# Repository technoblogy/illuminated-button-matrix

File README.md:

# Illuminated Button Matrix
A 4 x 4 matrix of illuminated pushbuttons with a two-wire I2C interface, controlled by an ATtiny88, that you can use for games, music, or control applications.
For more information see: http://www.technoblogy.com/show?1YJO.

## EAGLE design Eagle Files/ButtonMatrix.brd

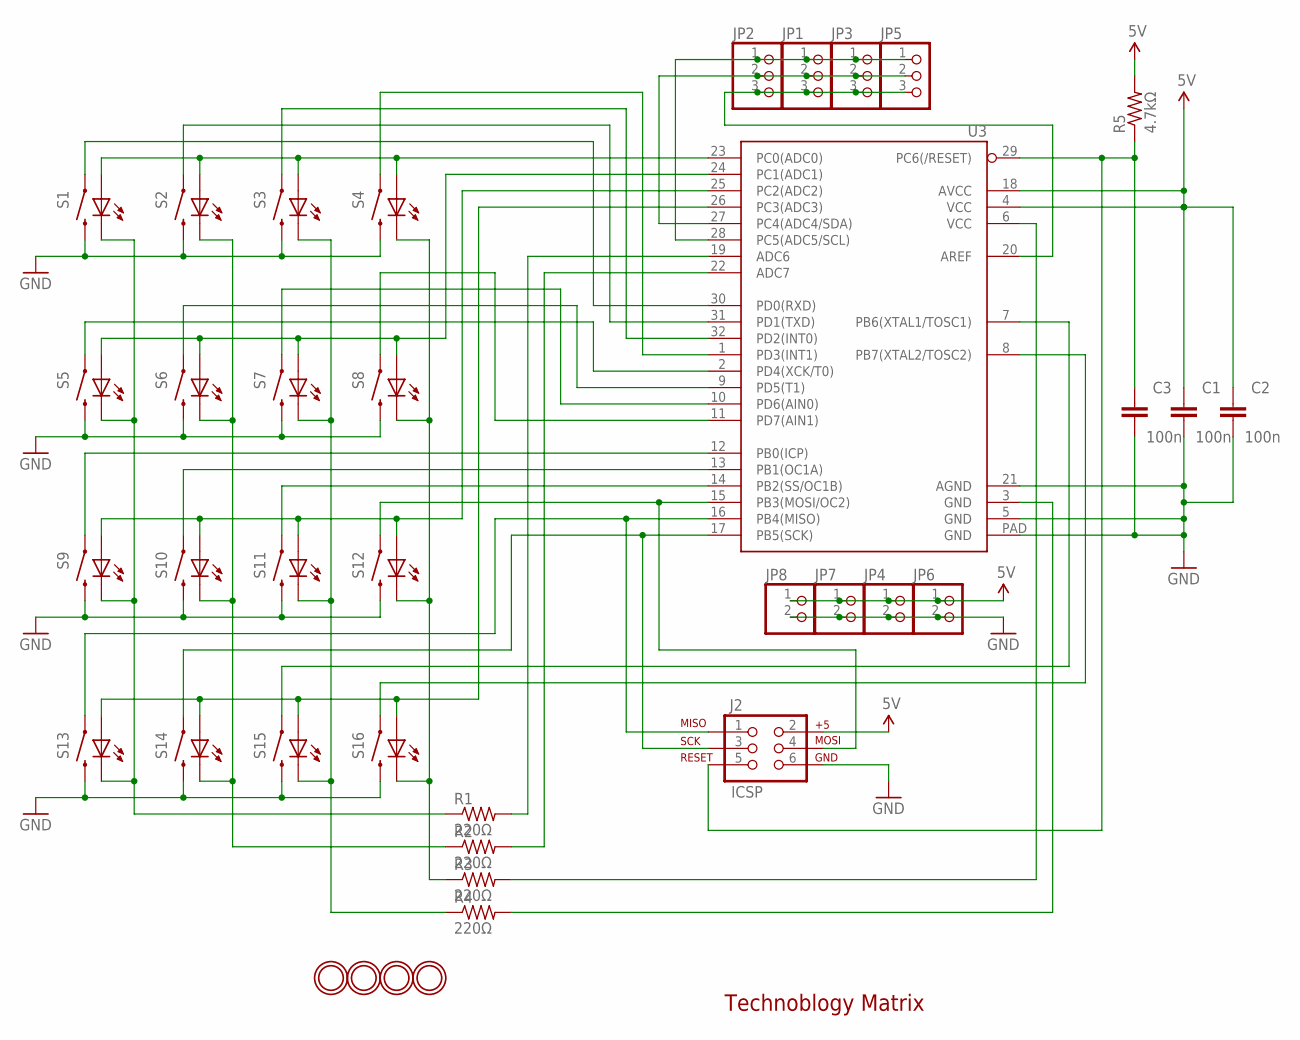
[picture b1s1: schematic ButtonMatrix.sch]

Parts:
C1, C2, C3: 100n; 0603-CAP
J2: ICSP; 2X3
JP1, JP2, JP3, JP5: HEADER-1X3EDGESMT; 1X03_EDGESMT
JP4, JP6, JP7, JP8: HEADER-1X2EDGE; 1X02_EDGESMT
R1, R2, R3, R4: 220Ω; R0805
R5: 4.7kΩ; R0805
S1, S2, S3, S4, S5, S6, S7, S8, S9, S10, S11, S12, S13, S14, S15, S16: SWITCH-MOMENTARY-LEDPTH; TACTILE-PTH-LED-12MM
U3: ATMEGA328P_MLFMLF32; MLF32-PAD
U$1, U$2, U$3, U$4: MOUNTINGHOLE2.5; MOUNTINGHOLE_2.5_PLATED

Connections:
5V: C1.1, C2.1, J2.2, JP4.1, JP6.1, JP7.1, JP8.1, R5.2, U3.4 (VCC), U3.18 (AVCC)
GND: C1.2, C2.2, C3.2, J2.6, JP4.2, JP6.2, JP7.2, JP8.2, S1.2, S2.2, S3.2, S4.2, S5.2, S6.2, S7.2, S8.2, S9.2, S10.2, S11.2, S12.2, S13.2, S14.2, S15.2, S16.2, U3.5 (GND), U3.21 (AGND), U3.PAD (GND)
unnamed: S9.A, S10.A, S11.A, S12.A, U3.25 (PC2(ADC2))
unnamed: R1.1, S1.C, S5.C, S9.C, S13.C
unnamed: R2.1, S2.C, S6.C, S10.C, S14.C
unnamed: R3.2, U3.6 (VCC)
unnamed: S1.4 (1), U3.30 (PD0(RXD))
unnamed: R3.1, S4.C, S8.C, S12.C, S16.C
unnamed: S2.4 (1), U3.31 (PD1(TXD))
unnamed: S3.4 (1), U3.32 (PD2(INT0))
unnamed: S4.4 (1), U3.1 (PD3(INT1))
unnamed: S5.4 (1), U3.2 (PD4(XCK/T0))
unnamed: S6.4 (1), U3.9 (PD5(T1))
unnamed: S7.4 (1), U3.10 (PD6(AIN0))
unnamed: S8.4 (1), U3.11 (PD7(AIN1))
unnamed: S9.4 (1), U3.12 (PB0(ICP))
unnamed: S10.4 (1), U3.13 (PB1(OC1A))
unnamed: S11.4 (1), U3.14 (PB2(SS/OC1B))
unnamed: J2.4, S12.4 (1), U3.15 (PB3(MOSI/OC2))
unnamed: J2.1, S13.4 (1), U3.16 (PB4(MISO))
unnamed: J2.3, S14.4 (1), U3.17 (PB5(SCK))
unnamed: S15.4 (1), U3.7 (PB6(XTAL1/TOSC1))
unnamed: S16.4 (1), U3.8 (PB7(XTAL2/TOSC2))
unnamed: S1.A, S2.A, S3.A, S4.A, U3.23 (PC0(ADC0))
unnamed: S5.A, S6.A, S7.A, S8.A, U3.24 (PC1(ADC1))
unnamed: S13.A, S14.A, S15.A, S16.A, U3.26 (PC3(ADC3))
unnamed: JP1.2, JP2.2, JP3.2, JP5.2, U3.27 (PC4(ADC4/SDA))
unnamed: JP1.1, JP2.1, JP3.1, JP5.1, U3.28 (PC5(ADC5/SCL))
unnamed: JP1.3, JP2.3, JP3.3, JP5.3, U3.20 (AREF)
unnamed: R2.2, U3.22 (ADC7)
unnamed: R1.2, U3.19 (ADC6)
unnamed: C3.1, J2.5, R5.1, U3.29 (PC6(/RESET))
unnamed: R4.2, U3.3 (GND)
unnamed: R4.1, S3.C, S7.C, S11.C, S15.C

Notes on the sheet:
Technoblogy Matrix

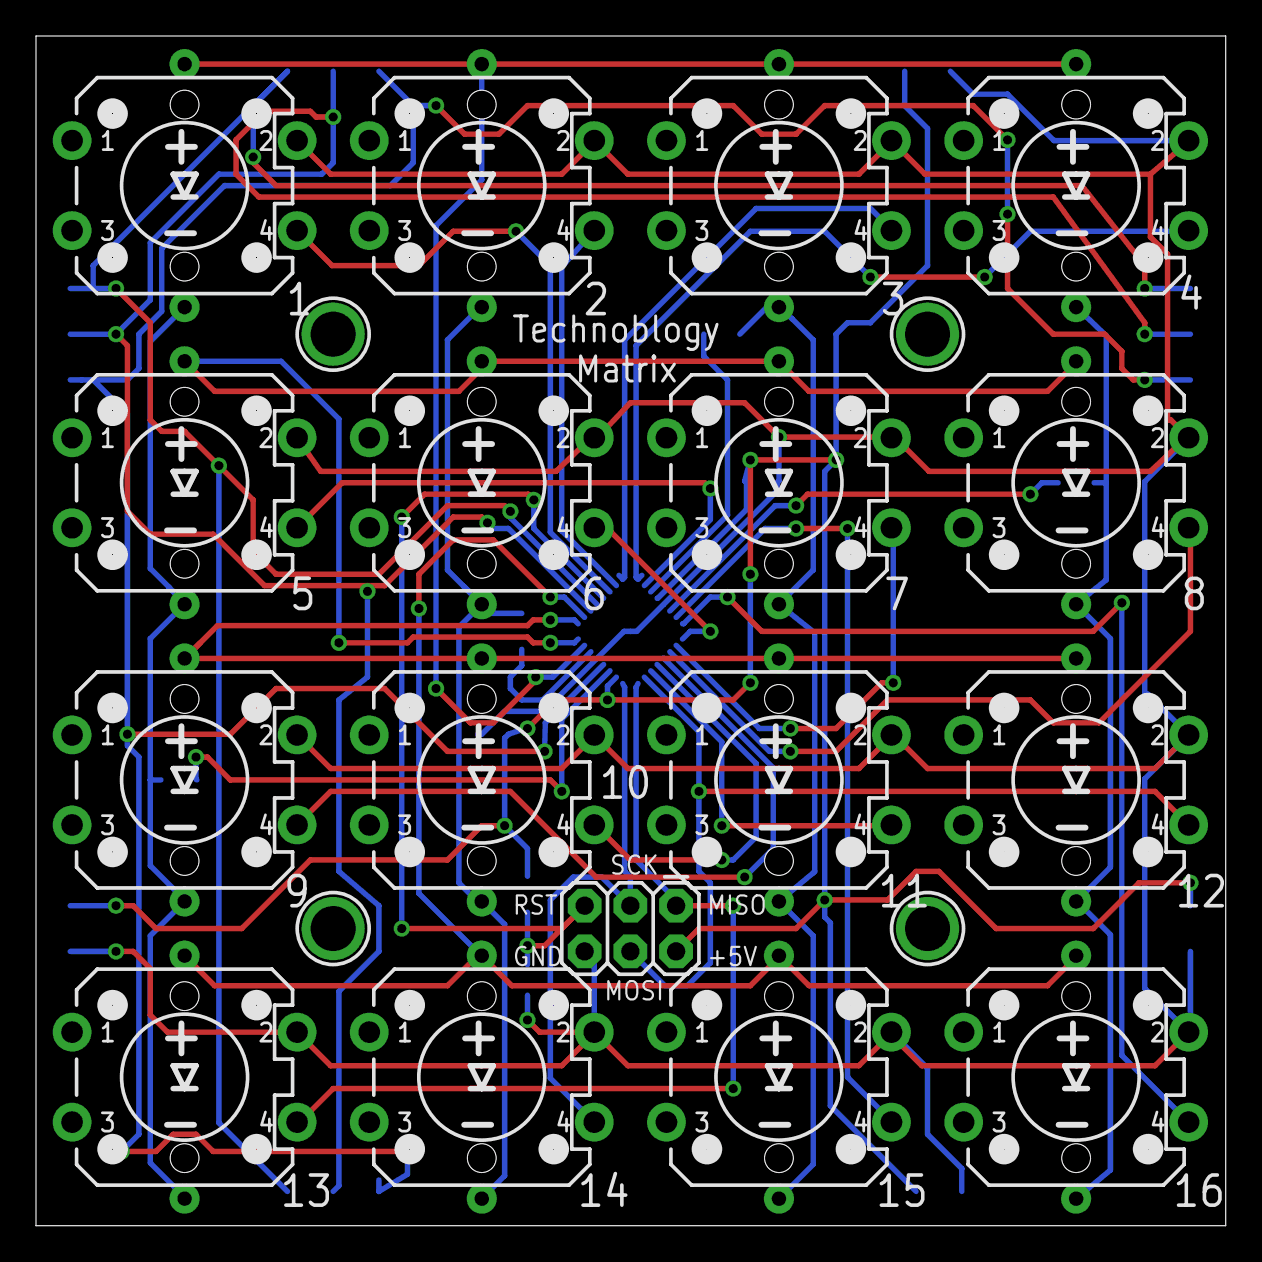
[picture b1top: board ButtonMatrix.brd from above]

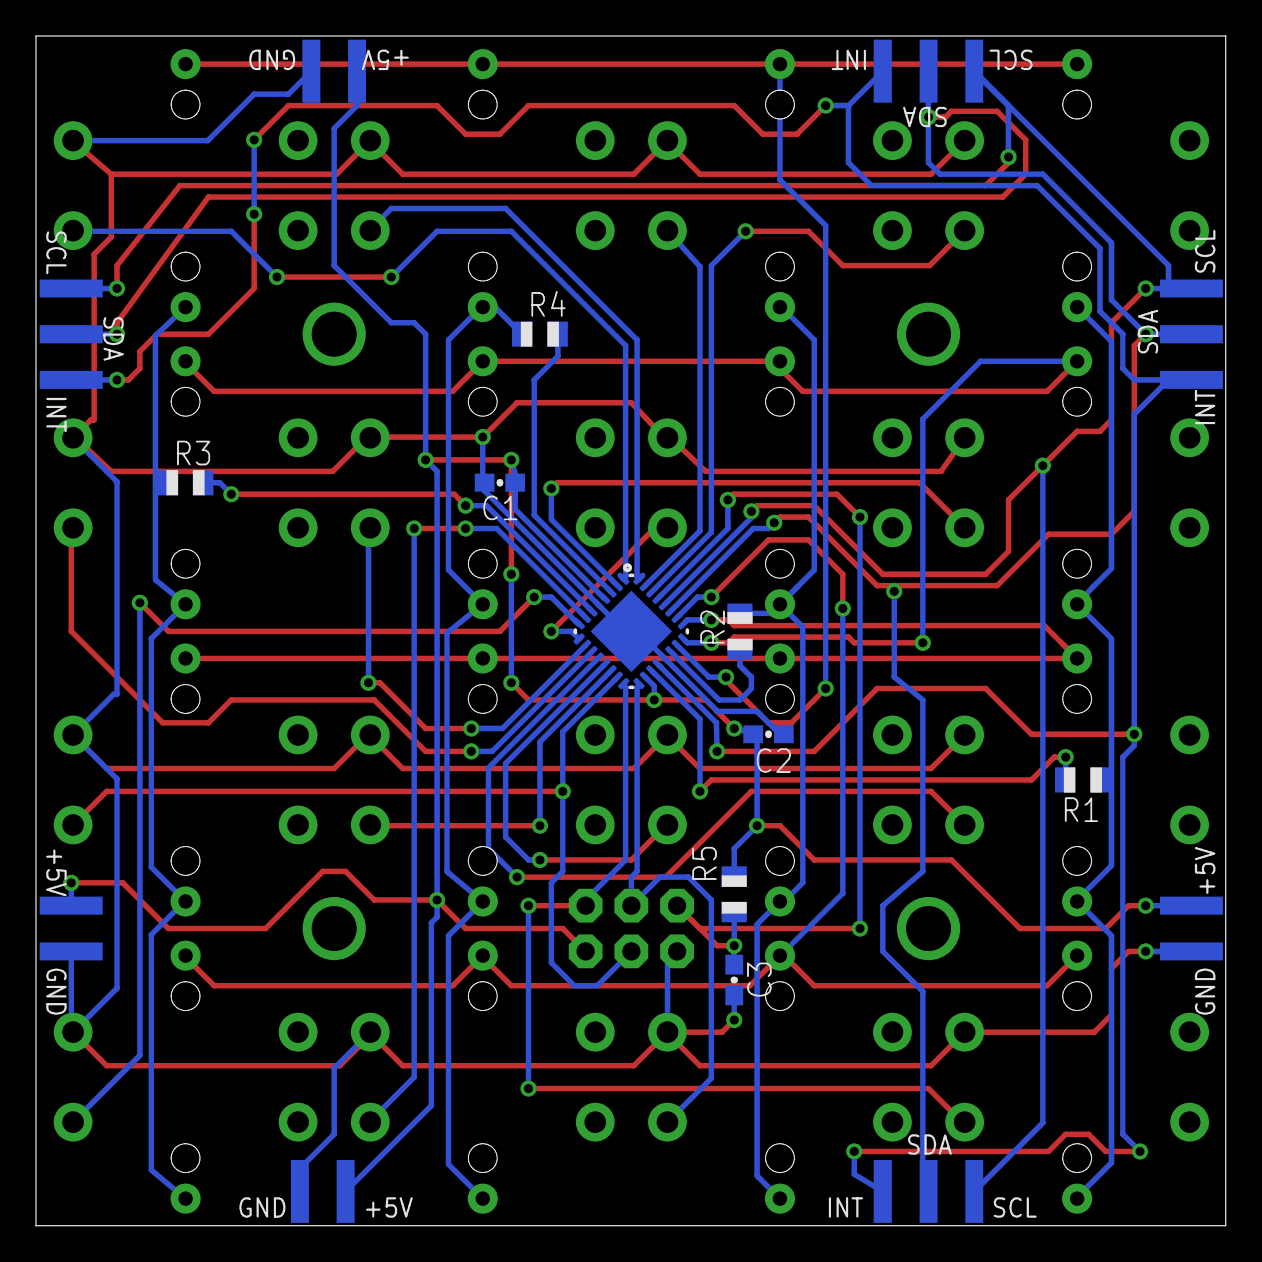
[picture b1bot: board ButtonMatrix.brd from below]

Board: 2 copper layers, 66.1 x 66.1 mm, 38 parts (17 on the bottom side), 34 nets.

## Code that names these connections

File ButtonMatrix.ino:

/* Illuminated Button Matrix

   David Johnson-Davies - www.technoblogy.com - 9th May 2019
   ATtiny88 @ 8MHz (internal oscillator; BOD disabled)
   
   CC BY 4.0
   Licensed under a Creative Commons Attribution 4.0 International license: 
   http://creativecommons.org/licenses/by/4.0/
*/

#include <Wire.h>

volatile int Lights;           // One bit per light; bit 0 = Button 1 etc.
volatile int Keys;             // One bit per key; bit 0 = Button 1 etc.
int Row;

// INT pin **********************************************

const int IntPin = PORTC7;

inline void IntLow () {
  PORTC = PORTC & ~(1<<IntPin);
  DDRC = DDRC | 1<<IntPin;
}

inline void IntRelease () {
  DDRC = DDRC & ~(1<<IntPin);
  PORTC = PORTC | 1<<IntPin;
}

// I2C Interface **********************************************

const int I2CAddress = 0x3A;

void SetLights (int nBytes) {
  (void) nBytes;
  uint8_t Low = Wire.read();
  uint8_t High = Wire.read();
  Lights = High<<8 | Low;
}

void GetKeys () {
  int SendData = ReadKeys();
  Wire.write(SendData & 0xFF);
  Wire.write(SendData>>8 & 0xFF);
  IntRelease();
}

// Keys **********************************************

void SetupKeys () {
  // Set up pin change interrupts on the keys
  DDRB = 0; PORTB = 0xFF;       // Port B all input pullups
  DDRD = 0; PORTD = 0xFF;       // Port D all input pullups
  PCMSK0 = 0xFF; PCMSK2 = 0xFF; // Enable PB0 to PB7 and PD0 to PD7
  PCIFR = 1<<PCIF2 | 1<<PCIF0;  // Clear interrupt flags
  PCICR = 1<<PCIE2 | 1<<PCIE0;  // Enable interrupts
  // Set up INT pin PC7 as INPUT_PULLUP
  IntRelease();
}

int ReadKeys () {
  int Count = 0, Keys, LastKeys = -1;
  // Wait until keys are stable
  do {
    Keys = ~(PINB<<8 | PIND);
    Count++;
    if (LastKeys != Keys) Count = 0;
    LastKeys = Keys;
  } while (Count < 7);
  return Keys;
} 
  
ISR(PCINT0_vect) {
  IntLow();
}

ISR(PCINT2_vect) {
  IntLow();
}

// Light multiplexing **********************************************

void SetupLights () {
  // Set up Timer/Counter1 to multiplex the display
  TCCR1A = 0<<WGM10;            // CTC mode
  TCCR1B = 1<<WGM12 | 2<<CS10;  // CTC mode; divide by 8 = 62500Hz
  OCR1A = 249;                  // Divide by 250 -> 250Hz
  TIMSK1 = TIMSK1 | 1<<OCIE1A;  // Enable compare match interrupt
  // Make LED rows and columns outputs
  DDRC = DDRC | 0x0F;
  DDRA = DDRA | 0x0F;
}

void DisplayNextRow() {
  PORTC = PORTC & ~(0x0F);      // Take rows low
  Row = (Row+1) & 0x03;
  uint8_t Bits = Lights>>(Row*4) & 0x0F;
  PORTA = ~Bits;
  PORTC = PORTC | 1<<Row;       // Take row bit high
}

// Timer/Counter0 interrupt - multiplexes display
ISR(TIMER1_COMPA_vect) {
  DisplayNextRow();
}

// Setup **********************************************

void setup (void) {
  SetupLights();
  SetupKeys();
  // Initialise I2C Slave
  Wire.begin(I2CAddress);
  Wire.onReceive(SetLights);
  Wire.onRequest(GetKeys);
}
 
// Everything under interrupt
void loop (void) {
}

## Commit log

2019-05-09 Version 1 - 9th May 2019
2019-05-09 Version 1 - 9th Mar 2019

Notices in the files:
parts and their libraries:
microbuilder: This work is placed in the public domain, and may be freely used for commercial and non-commercial work with the following conditions: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
SparkFun-Electromechanical: Licensing: Creative Commons ShareAlike 4.0 International - https://creativecommons.org/licenses/by-sa/4.0
